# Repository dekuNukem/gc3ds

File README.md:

gc3ds is a 3DS modification that allows user to use Nintendo GameCube controller to play any games on Nintendo 3DS consoles. This open-source project uses an Arduino Nano to read the state of GameCube controller, then mirror them to Nintendo 3DS with a maximum delay of no more than 1/1000 seconds (1 millisecond). Users can also choose to customize button mappings between gc controller and 3DS with a LCD screen. 

For all the resources about this project(video, parts list, guides, etc), see http://goo.gl/SyRLb5

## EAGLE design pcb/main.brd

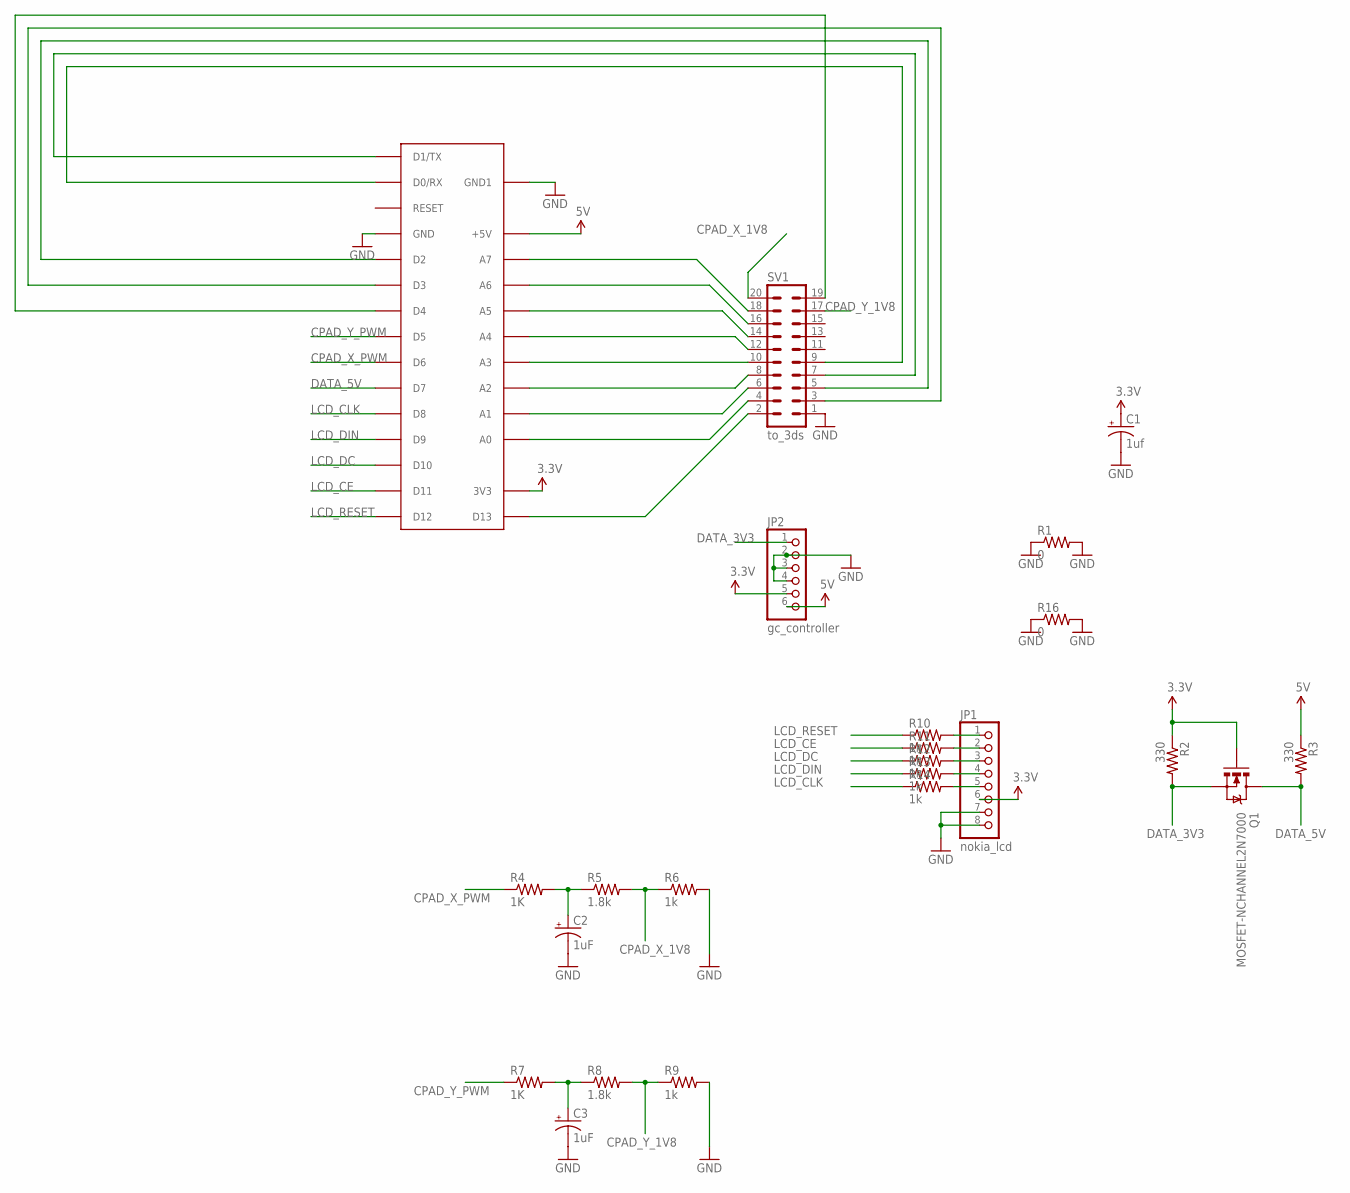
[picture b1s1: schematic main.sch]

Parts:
C1: 1uf; CPOL-RADIAL-10UF-25V
C2, C3: 1uF; CPOL-RADIAL-10UF-25V
JP1: nokia_lcd; 1X08-CLEANBIG
JP2: gc_controller; 1X06
Q1: MOSFET-NCHANNEL2N7000; TO-92
R1, R16: 0; AXIAL-0.4
R2, R3: 330; AXIAL-0.4
R4, R7: 1K; AXIAL-0.4
R5, R8: 1.8k; AXIAL-0.4
R6, R9, R10, R11, R12, R13, R14: 1k; AXIAL-0.4
SV1: to_3ds; MA10-2
U$1: ARDUINONANO; PDIP-32

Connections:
3.3V: C1.1 (+), JP1.6, JP2.5, Q1.2 (G), R2.P$1 (1), U$1.3V3
5V: JP2.6, R3.P$1 (1), U$1.+5V
CPAD_X_1V8: R5.P$2 (2), R6.P$1 (1), SV1.20
CPAD_X_PWM: R4.P$1 (1), U$1.D6
CPAD_Y_1V8: R8.P$2 (2), R9.P$1 (1), SV1.17
CPAD_Y_PWM: R7.P$1 (1), U$1.D5
DATA_3V3: JP2.1, Q1.1 (S), R2.P$2 (2)
DATA_5V: Q1.3 (D), R3.P$2 (2), U$1.D7
GND: C1.2 (-), C2.2 (-), C3.2 (-), JP1.7, JP1.8, JP2.2, JP2.3, JP2.4, R1.P$1 (1), R1.P$2 (2), R6.P$2 (2), R9.P$2 (2), R16.P$1 (1), R16.P$2 (2), SV1.1, U$1.GND, U$1.GND1
LCD_CE: R11.P$1 (1), U$1.D11
LCD_CLK: R14.P$1 (1), U$1.D8
LCD_DC: R12.P$1 (1), U$1.D10
LCD_DIN: R13.P$1 (1), U$1.D9
LCD_RESET: R10.P$1 (1), U$1.D12
unnamed: C2.1 (+), R4.P$2 (2), R5.P$1 (1)
unnamed: JP1.1, R10.P$2 (2)
unnamed: JP1.2, R11.P$2 (2)
unnamed: JP1.3, R12.P$2 (2)
unnamed: C3.1 (+), R7.P$2 (2), R8.P$1 (1)
unnamed: JP1.4, R13.P$2 (2)
unnamed: JP1.5, R14.P$2 (2)
unnamed: SV1.2, U$1.D13
unnamed: SV1.4, U$1.A0
unnamed: SV1.6, U$1.A1
unnamed: SV1.8, U$1.A2
unnamed: SV1.10, U$1.A3
unnamed: SV1.12, U$1.A4
unnamed: SV1.14, U$1.A5
unnamed: SV1.16, U$1.A6
unnamed: SV1.18, U$1.A7
unnamed: SV1.19, U$1.D4
unnamed: SV1.3, U$1.D3
unnamed: SV1.5, U$1.D2
unnamed: SV1.7, U$1.D1/TX
unnamed: SV1.9, U$1.D0/RX

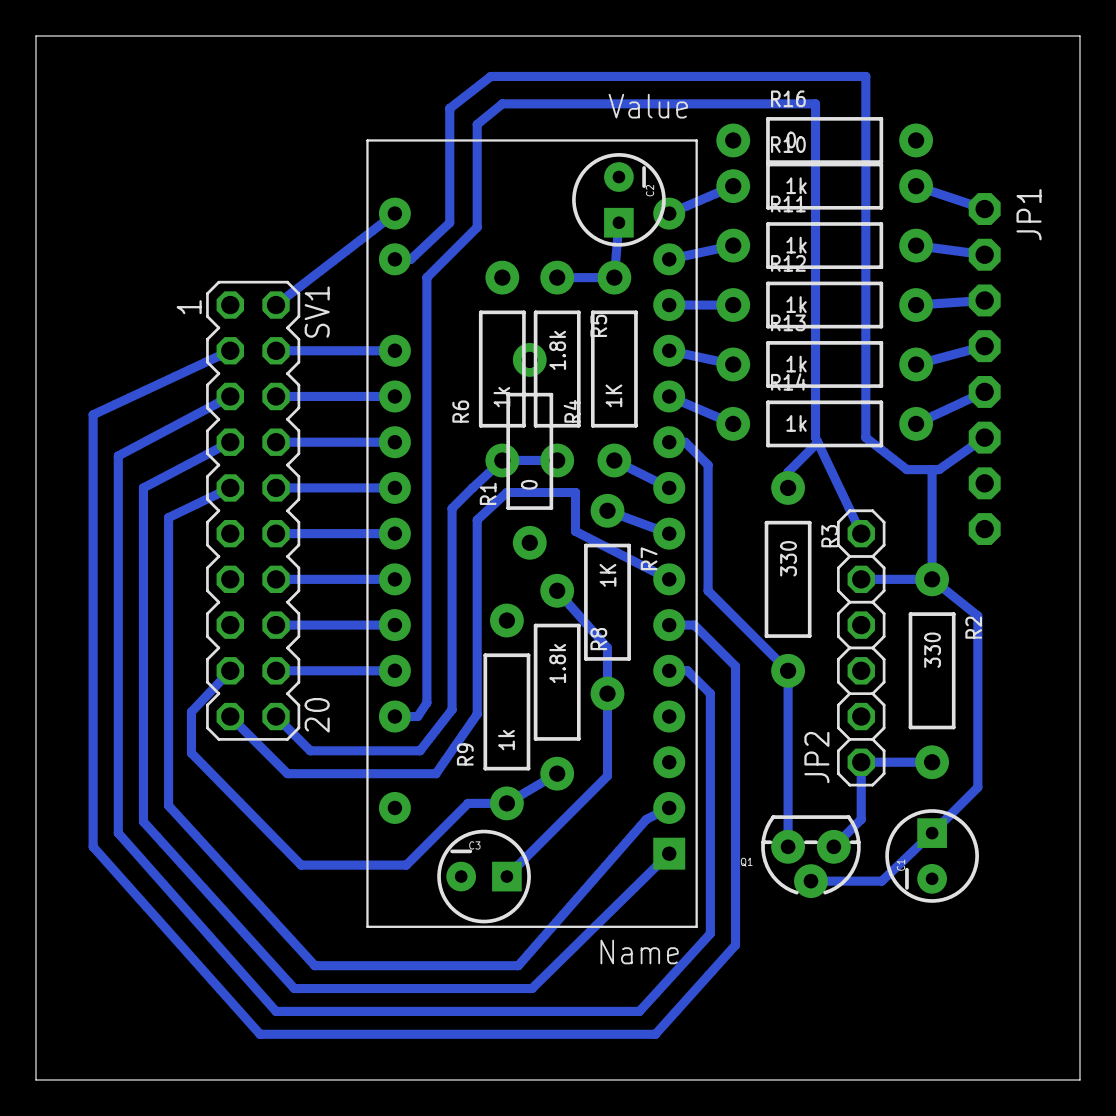
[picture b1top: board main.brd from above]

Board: 2 copper layers, 58.0 x 58.0 mm, 23 parts (0 on the bottom side), 35 nets.

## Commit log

2014-09-25 remove file1.txt
2014-09-25 added Nintendo library
2014-09-25 added README
2014-09-25 clean up/bug fix
2014-09-25 added comments
2014-10-01 updated low pass filter
2014-10-04 added s-stick side smash and many-to-one button mapping
2014-10-04 introduced overview page
2014-10-07 built-in c-pad selector
2014-10-07 build-in c-pad selector cleaned up

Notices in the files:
parts and their libraries:
SparkFun-DiscreteSemi: Licensing: Creative Commons ShareAlike 4.0 International - https://creativecommons.org/licenses/by-sa/4.0
